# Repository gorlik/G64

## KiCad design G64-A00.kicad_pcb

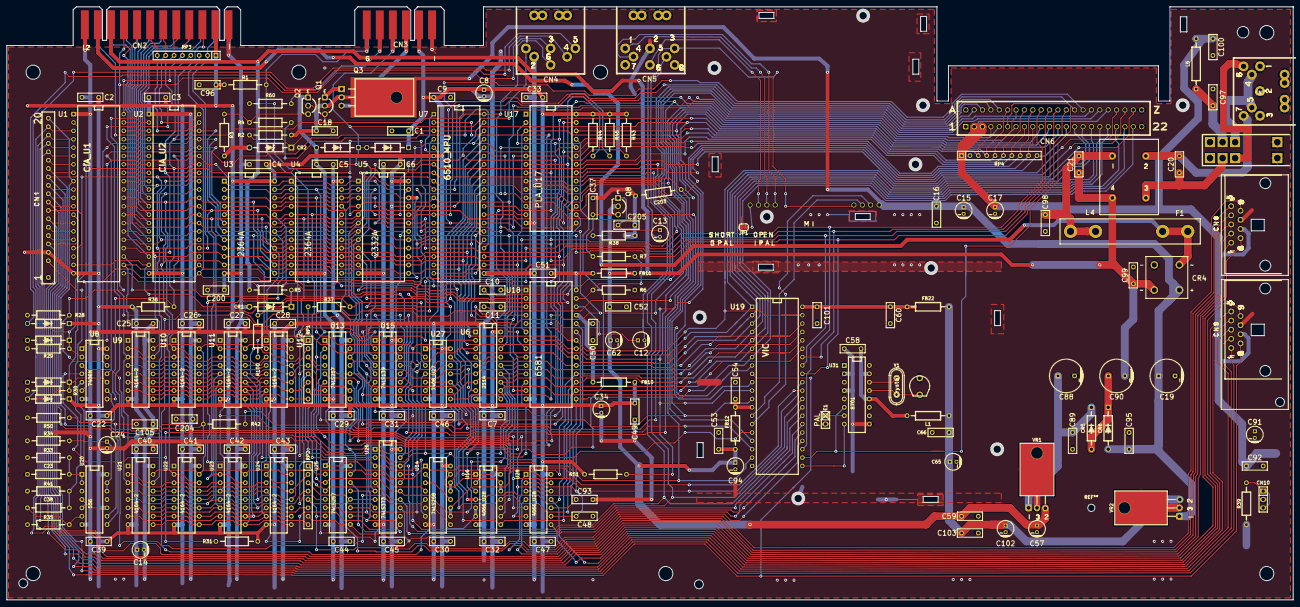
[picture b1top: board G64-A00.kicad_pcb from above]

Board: 2 copper layers, 390.0 x 179.8 mm, 181 parts (0 on the bottom side), 191 nets.

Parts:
C1, C2, C3, C4, C5, C6, C7, C9, C16, C18, C22, C25, C26, C27, C28, C29, C30, C31, C32, C33, C39, C40, C41, C42, C43, C44, C45, C46, C47, C49, C50, C51, C52, C53, C54, C59, C60, C89, C92, C95, C96, C98, C99, C101, C103, C105, C200: .1; C_film_7x2.5
C8, C12, C13, C14, C15, C17, C24, C34, C57, C62, C65, C94, C102: 10uF; CP_5p2x11
C10, C11: 470pF; C_film_7x2.5
C19: 2200uF; CP_10p5x20
C20, C21, C97, C100: .22; C_film_7x2.5
C23: 360pF; CAP_AXIAL_P12.7mm
C37: 1000pF; C_film_7x2.5
C38: 4.7nF; CAP_AXIAL_P12.7mm
C48, C93: 1800pF; C_film_7x2.5
C58: .22uF; C_film_7x2.5
C66: .1uF; C_film_7x2.5
C88: 1000uF; CP_10p5x20
C90: 470uF; CP_10p5x20
C91: 100uF; CP_5p2x11
C203: 82pF; CAPACITOR_RADIAL_P13.97_L9.9_D3.6
C204: NC; C_film_7x2.5
C205: 220pF; C_film_7x2.5
CN1: KEYBOARD_20PIN_MALE; KEYBOARD_CON
CN2: USER_PORT_CON; EDGE_CON_24P
CN3: CASSETTE_PORT_CON; EDGE_CON_12P_TAPE
CN4: SERIAL_BUS_CON; SERIAL_CON_DIN6
CN5: AV_CONN; AV_CON_DIN8
CN6: EXPANSION_PORT
CN7: POWER_CON; POWER_CON_D7_250407
CN8, CN9: CONTROL_PORT; JOYPORT_DB9
CN10: LED_CONNECTOR; pin_strip_3
CR1: IN4371; ZENER_12.7mm
CR2: IN755; ZENER_12.7mm
CR4: BRIDGE_RECTIFIER
CR5, CR6: 1N4001; RECTIFIER_TH_P12.7mm
CR9, CR12, CR13, CR14, CR15, CR16: D_Small_ALT; RECTIFIER_TH_P12.7mm
CT1: 22pF; CAP_trim_5.08mm
E1: JUMPER_WIRE; pin_strip_2
F1: 1A; FUSE
FB10, FB11, FB12, FB22: FERRITE_BEAD; FERRITE_BEAD_TH_P12.7mm
JP1: Jumper_NC_Small; SolderJumper-2_P1.3mm_Bridged_RoundedPad1.0x1.5mm
L1: L; RESISTOR
L4: CHOKE
L5: 1.2uH; INDUCTOR_P15.24mm
M1: MODULATOR_LONGBOARD; MODULATOR_PORT_LONGBOARD
Q1, Q2, Q8: 2SC1815; Q_NPN_ECB
Q3: TP29B/2SD880; TO-220-3_Horizontal_TabDown_250407
R1, R43, R44, R45: 3K3; r_0250p12_7
R2, R51: 1.5K; r_0250p12_7
R3, R7: 10K; r_0250p12_7
R4, R6, R28, R29, R30, R31, R36, R38, R100: 1K; r_0250p12_7
R5: 560; r_0250p12_7
R33, R34: 47K; r_0250p12_7
R35: 470K; r_0250p12_7
R37: 2K7; r_0250p12_7
R39: 390; r_0250p12_7
R41, R50: 1M; r_0250p12_7
R42: 82; r_0250p12_7
R60: 100; r_0250p12_7
RP1, RP2: 33R isolated; rpak_sil_8
RP3: 3K3 Bussed; rpak_sil_8
RP4: 3K3 Bussed; rpak_sil_10
SW1: POWER_SWITCH
U1: CIA_U1; DIP-40_600
U2: CIA_U2; DIP-40_600
U3, U4: 2364A; DIP-24_600
U5: 2332A; DIP-24_600
U6: 2114; DIP-18_300
U7: 6510_MPU; DIP-40_600
U8: 7406N; DIP-14_300
U9, U10, U11, U12, U21, U22, U23, U24: 4164-2; DIP-16_300
U13, U25: 74LS257; DIP-16_300
U14: 74LS258; DIP-16_300
U15: 74LS139; DIP-16_300
U16, U28: 4066_U28; DIP-14_300
U17: PLA_U17; DIP-28_600
U18: 6581; DIP-28_600
U19: VIC; DIP-40_600
U20: 556; DIP-14_300
U26: 74LS373; DIP-20_300
U27: 7408_U27; DIP-14_300
U31: 8701; DIP-16_300
VR1: 7812; VREG_TO-220-3_Horizontal_TabDown
VR2: 7805; VREG_TO-220-3_Horizontal_TabDown
Y1: Crystal; XTAL_PTH_HC-49US

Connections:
+5V: C1.1, C2.1, C3.2, C4.2, C5.2, C6.2, C7.1, C8.1, C9.1, C14.1, C17.1, C22.1, C25.1, C26.1, C27.1, C28.1, C29.2, C30.1, C31.2, C32.2, C33.1, C34.1, C39.2, C40.1, C41.1, C42.1, C43.1, C44.2, C45.1, C46.1, C47.1, C49.1, C91.1, C92.1, C96.2, C100.2, CN1.4, CN2.2, CN3.B,2, CN6.2, CN6.3, CN8.7, CN9.7, CR9.1, CR13.1, CR14.1, FB10.2, L5.1, R1.1, R28.2, R29.2, R30.2, R31.2, R33.1, R34.1, R35.1, R36.1, R39.1, R41.1, R43.1, R44.1, R45.1, R50.1, R51.2, RP3.1, RP4.1, U1.20, U2.20, U3.24, U4.24, U5.21, U5.24, U6.18, U7.6, U8.14, U9.8, U10.8, U11.8, U12.8, U13.16, U14.16, U15.16, U16.14, U17.28, U20.4, U20.10, U20.14, U21.8, U22.8, U23.8, U24.8, U25.16, U26.20, U27.1, U27.14, U28.14
+9V_UNREG: C15.1, C16.1, C18.1, C19.1, C95.1, CR4.1, CR6.2, M1.1, Q1.2, Q3.2, R2.1, VR2.1
+12V: C52.1, C53.1, C57.1, C59.1, C62.1, C94.1, FB11.2, FB12.2, Q8.2, VR1.2
/5V_IN: C97.2, L5.2, SW1.4
/9VAC: C21.2, C90.2, C99.2, CN2.10, CR4.4, L4.4, R5.1
/9VAC': CN2.11, CR4.2, F1.1
/9V_F: C21.1, C98.1, F1.2, L4.1
/9V_IN: C20.2, L4.3, SW1.1
/9V_IN': C20.1, CN7.7, L4.2
/60Hz: R37.2, U1.19, U2.19, U27.3
/ATN: CN2.9, CN4.3, R28.1, U8.12
/ATN_OUT: U2.5, U8.13
/BTNB: CN1.16, CN8.6, U1.6
/CASS_MOTOR: R4.2, U7.24
/CASS_PWR: CN3.C,3, Q3.3
/CASS_RD: CN3.D,4, CN4.1, CR9.2, CR12.1, RP3.4, U1.24
/CASS_SENSE: CN3.F,6, R1.2, U7.25
/CASS_WRT: R60.2, U7.26
/CASS_WRT': CN3.E,5, R60.1
/CLK: CN4.4, CR14.2, CR16.1, R30.1, U2.8, U8.10
/CLK_OUT: U2.6, U8.11
/CNT1: CN2.4, RP3.5, U1.40
/CNT2: CN2.6, RP3.7, U2.40
/COL0: CN1.13, CN8.1, U1.2
/COL1: CN1.19, CN8.2, U1.3
/COL2: CN1.18, CN8.3, U1.4
/COL3: CN1.17, CN8.4, U1.5
/COL5: CN1.15, U1.7
/COL6: CN1.14, U1.8, U28.6, U28.12
/COL7: CN1.20, U1.9, U28.5, U28.13
/DATA: CN4.5, CR13.2, CR15.1, R29.1, U2.9, U8.2
/DATA_OUT: U2.7, U8.1
/G64-A00_sheet2/AEC: U8.3, U14.15, U16.5, U16.6, U16.12, U16.13, U19.16, U26.1, U27.4, U27.12
/G64-A00_sheet2/AUDIO_IN: C12.2, CN5.5
/G64-A00_sheet2/AUDIO_OUT: C13.2, CN5.3, M1.4
/G64-A00_sheet2/BA: CN6.12, U17.26, U19.12, U27.9
/G64-A00_sheet2/CHROMA: M1.3, U19.14
/G64-A00_sheet2/CHROMA_O: CN5.6, M1.7
/G64-A00_sheet2/COMP_O: CN5.4, M1.5
/G64-A00_sheet2/GR\~W~: U6.10, U17.13
/G64-A00_sheet2/LUMA: M1.2, U19.15
/G64-A00_sheet2/LUMA_O: CN5.1, M1.6
/G64-A00_sheet2/MA0: RP2.4, U9.5, U10.5, U11.5, U12.5, U21.5, U22.5, U23.5, U24.5
/G64-A00_sheet2/MA1: RP2.8, U9.7, U10.7, U11.7, U12.7, U21.7, U22.7, U23.7, U24.7
/G64-A00_sheet2/MA2: RP2.6, U9.6, U10.6, U11.6, U12.6, U21.6, U22.6, U23.6, U24.6
/G64-A00_sheet2/MA3: RP2.2, U9.12, U10.12, U11.12, U12.12, U21.12, U22.12, U23.12, U24.12
/G64-A00_sheet2/MA4: RP1.4, U9.11, U10.11, U11.11, U12.11, U21.11, U22.11, U23.11, U24.11
/G64-A00_sheet2/MA5: RP1.6, U9.10, U10.10, U11.10, U12.10, U21.10, U22.10, U23.10, U24.10
/G64-A00_sheet2/MA6: RP1.2, U9.13, U10.13, U11.13, U12.13, U21.13, U22.13, U23.13, U24.13
/G64-A00_sheet2/MA7: RP1.8, U9.9, U10.9, U11.9, U12.9, U21.9, U22.9, U23.9, U24.9
/G64-A00_sheet2/SID_VCC: C50.1, FB10.1, U18.25
/G64-A00_sheet2/SID_VDD: C51.1, FB11.1, U18.28
/G64-A00_sheet2/VA0: RP2.3, U19.24, U25.12, U26.7
/G64-A00_sheet2/VA1: RP2.7, U19.25, U25.9, U26.13
/G64-A00_sheet2/VA2: RP2.5, U19.26, U25.7, U26.8
/G64-A00_sheet2/VA3: RP2.1, U19.27, U25.4, U26.14
/G64-A00_sheet2/VA4: RP1.3, U13.12, U17.20, U19.28, U26.17
/G64-A00_sheet2/VA5: RP1.5, U13.7, U17.21, U19.29, U26.18
/G64-A00_sheet2/VA6: RP1.1, U13.4, U14.4, U26.4
/G64-A00_sheet2/VA6': U14.13, U14.14, U19.30
/G64-A00_sheet2/VA7: RP1.7, U13.9, U14.7, U26.3
/G64-A00_sheet2/VA7': U14.10, U14.11, U19.31
/G64-A00_sheet2/VIC_VCC: C60.1, C101.1, FB22.1, U19.40
/G64-A00_sheet2/VIC_VDD: C54.1, FB12.1, U19.13
/G64-A00_sheet2/~AEC~: R31.1, U8.4, U13.15, U17.25, U25.15
/G64-A00_sheet2/~BASIC~: U3.20, U17.17
/G64-A00_sheet2/~CASRAM~: R42.2, U17.18
/G64-A00_sheet2/~CASRAM~': C204.2, R42.1, U9.15, U10.15, U11.15, U12.15, U21.15, U22.15, U23.15, U24.15
/G64-A00_sheet2/~CAS~: C203.2, U13.1, U14.1, U17.9, U19.19, U25.1
/G64-A00_sheet2/~CHAROM~: U5.20, U17.15
/G64-A00_sheet2/~CIAS~: U15.7, U15.15
/G64-A00_sheet2/~COLOR~: U15.6, U27.13
/G64-A00_sheet2/~DMA~: CN6.13, RP4.10, U27.5, U27.10
/G64-A00_sheet2/~EXROM~: CN6.9, RP4.9, U17.23
/G64-A00_sheet2/~GAME~: CN6.8, RP4.7, U17.22
/G64-A00_sheet2/~I\O~: U15.1, U17.12
/G64-A00_sheet2/~KERNAL: U4.20, U17.16
/G64-A00_sheet2/~RAS~: U9.4, U10.4, U11.4, U12.4, U19.18, U21.4, U22.4, U23.4, U24.4, U26.11
/G64-A00_sheet2/~ROMH~: CN6.B, U17.10
/G64-A00_sheet2/~ROML~: CN6.11, U17.11
/G64-A00_sheet2/~SID~: U15.5, U18.8
/G64-A00_sheet2/~VIC~: U15.4, U19.10
/JOYA0: CN1.12, CN9.1, U1.10
/JOYA1: CN1.11, CN9.2, U1.11
/JOYA2: CN1.10, CN9.3, U1.12
/JOYA3: CN1.5, CN9.4, U1.13
/LED+: CN10.1, CN10.3, R39.2
/PA2: CN2.M, U2.4
/PB0: CN2.C, U2.10
/PB1: CN2.D, U2.11
/PB2: CN2.E, U2.12
/PB3: CN2.F, U2.13
/PB4: CN2.H, U2.14
/PB5: CN2.J, U2.15
/PB6: CN2.K, U2.16
/PB7: CN2.L, U2.17
/POTAX: CN9.9, U28.8
/POTAY: CN9.5, U28.11
/POTBX: CN8.9, U28.1
/POTBY: CN8.5, U28.4
/ROW5: CN1.7, U1.15
/ROW6: CN1.6, U1.16
/ROW7: CN1.9, U1.17
/SP1: CN2.5, RP3.6, U1.39
/SP2: CN2.7, RP3.8, U2.39
/TRIGA: C38.1, R35.2, U20.6
/~FLAG2~: CN2.B, RP3.2, U2.24
/~PC2~: CN2.8, U2.18
/~RESTORE~: C38.2, CN1.3, R41.2
A0: CN6.Y, U1.38, U2.38, U3.8, U4.8, U5.8, U6.5, U7.7, U18.9, U25.13, U26.6
A1: CN6.X, U1.37, U2.37, U3.7, U4.7, U5.7, U6.6, U7.8, U18.10, U25.10, U26.12
A2: CN6.W, U1.36, U2.36, U3.6, U4.6, U5.6, U6.7, U7.9, U18.11, U25.6, U26.9
A3: CN6.V, U1.35, U2.35, U3.5, U4.5, U5.5, U6.4, U7.10, U18.12, U25.3, U26.15
A4: CN6.U, U3.4, U4.4, U5.4, U6.3, U7.11, U13.13, U18.13, U26.16
A5: CN6.T, U3.3, U4.3, U5.3, U6.2, U7.12, U13.6, U26.19
A6: CN6.S, U3.2, U4.2, U5.2, U6.1, U7.13, U13.3, U26.5
A7: CN6.R, U3.1, U4.1, U5.1, U6.17, U7.14, U13.10, U26.2
A8: CN6.P, U3.23, U4.23, U5.23, U6.16, U7.15, U15.14, U19.32, U25.14
A9: CN6.N, U3.22, U4.22, U5.22, U6.15, U7.16, U15.13, U19.33, U25.11
A10: CN6.M, U3.19, U4.19, U5.19, U7.17, U15.2, U19.34, U25.5
A11: CN6.L, U3.18, U4.18, U5.18, U7.18, U15.3, U19.23, U25.2
A12: CN6.K, RP4.8, U3.21, U4.21, U7.19, U13.14, U17.27
A13: CN6.J, RP4.6, U7.20, U13.5, U17.2
A14: CN6.H, RP4.5, U7.22, U13.2, U17.3
A15: CN6.F, RP4.4, U7.23, U13.11, U17.4
BTNA\~LP~: CN1.8, CN9.6, U1.14, U19.9
CAEC: U7.5, U27.6
CAN+5V: C65.1, C66.1, C102.1, C103.1, FB22.2, L1.2, VR2.2
D0: CN6.21, U1.33, U2.33, U3.9, U4.9, U5.9, U7.37, U16.11, U18.15, U19.7, U21.2, U21.14
D1: CN6.20, U1.32, U2.32, U3.10, U4.10, U5.10, U7.36, U9.2, U9.14, U16.8, U18.16, U19.6
D2: CN6.19, U1.31, U2.31, U3.11, U4.11, U5.11, U7.35, U16.4, U18.17, U19.5, U22.2, U22.14
D3: CN6.18, U1.30, U2.30, U3.13, U4.13, U5.13, U7.34, U10.2, U10.14, U16.1, U18.18, U19.4
D4: CN6.17, U1.29, U2.29, U3.14, U4.14, U5.14, U7.33, U18.19, U19.3, U23.2, U23.14
D5: CN6.16, U1.28, U2.28, U3.15, U4.15, U5.15, U7.32, U11.2, U11.14, U18.20, U19.2
D6: CN6.15, U1.27, U2.27, U3.16, U4.16, U5.16, U7.31, U18.21, U19.1, U24.2, U24.14
D7: CN6.14, U1.26, U2.26, U3.17, U4.17, U5.17, U7.30, U12.2, U12.14, U18.22, U19.39
DOT_CLOCK: CN6.6, U19.22, U31.6
GND: C1.2, C2.2, C3.1, C4.1, C5.1, C6.1, C7.2, C8.2, C9.2, C14.2, C15.2, C16.2, C17.2, C19.2, C22.2, C23.2, C24.2, C25.2, C26.2, C27.2, C28.2, C29.1, C30.2, C31.1, C32.1, C33.2, C34.2, C37.2, C39.1, C40.2, C41.2, C42.2, C43.2, C44.1, C45.2, C46.2, C47.2, C48.2, C49.2, C50.2, C51.2, C52.2, C53.2, C54.2, C57.2, C58.2, C59.2, C60.2, C62.2, C65.2, C66.2, C88.2, C89.2, C91.2, C92.2, C93.2, C94.2, C95.2, C96.1, C97.1, C98.2, C99.1, C100.1, C101.2, C102.2, C103.2, C105.1, C200.2, C203.1, C204.1, C205.2, CN1.1, CN2.1, CN2.12, CN2.A, CN2.N, CN3.A,1, CN4.2, CN5.2, CN6.1, CN6.22, CN6.A, CN6.Z, CN7.1, CN7.2, CN7.3, CN8.8, CN9.8, CN10.2, CR1.2, CR2.2, CR4.3, CR12.2, CR15.2, CR16.2, CT1.2, E1.2, JP1.2, Q2.1, R3.2, R6.1, R38.1, SW1.pe, U1.1, U2.1, U3.12, U4.12, U5.12, U6.9, U7.21, U8.7, U9.16, U10.16, U11.16, U12.16, U13.8, U14.8, U15.8, U16.7, U17.14, U17.19, U18.14, U19.20, U20.7, U21.16, U22.16, U23.16, U24.16, U25.8, U26.10, U27.7, U28.7, U31.2, U31.4, U31.9, VR1.3, VR2.3
unnamed: C10.1, U18.1
unnamed: C10.2, U18.2
unnamed: C11.1, U18.3
unnamed: C11.2, U18.4
unnamed: C12.1, U18.26
unnamed: C13.1, C205.1, Q8.1, R38.2
unnamed: C18.2, CR2.1, Q1.3, Q2.2, R2.2
unnamed: C23.1, R33.2, U20.1, U20.2
unnamed: C24.1, R34.2, U20.12, U20.13
unnamed: C37.1, Q8.3, R7.1
unnamed: C58.1, L1.1, U31.12, U31.15
unnamed: C88.1, C89.1, CR5.1, VR1.1
unnamed: C90.1, CR5.2, CR6.1
unnamed: C105.2, R50.2, U20.8
unnamed: C200.1, CR1.1, R5.2, R100.1
unnamed: CN6.7, U15.10
unnamed: CN6.10, U15.9
unnamed: CN7.4, CN7.5, SW1.5
unnamed: CN7.6, SW1.2
unnamed: CT1.1, U31.13, Y1.2
unnamed: E1.1, U31.7
unnamed: JP1.1, M1.8
unnamed: Q1.1, Q3.1
unnamed: Q2.3, R3.1, R4.1
unnamed: R6.2, R7.2, U18.27
unnamed: R37.1, R100.2, U27.2
unnamed: U14.6, U14.9
unnamed: U14.3, U14.12
unnamed: U6.11, U16.2, U19.35
unnamed: U6.12, U16.3, U19.36
unnamed: U6.13, U16.9, U19.37
unnamed: U6.14, U16.10, U19.38
unnamed: U8.5, U20.5
unnamed: U8.9, U20.9
unnamed: U6.8, U27.11
unnamed: U31.14, Y1.1
PHI0: U7.1, U19.17
PHI2: CN6.E, U1.25, U2.25, U7.39, U18.6
PHI_COLOR: U19.21, U31.8
POTX: C48.1, U18.24, U28.2, U28.9
POTY: C93.1, U18.23, U28.3, U28.10
RDY: U7.2, U27.8
R\~W~: CN6.5, R51.1, U1.22, U2.22, U7.38, U9.3, U10.3, U11.3, U12.3, U17.24, U18.7, U19.11, U21.3, U22.3, U23.3, U24.3
~CHAREN~: R43.2, U7.27, U17.6
~CIA1~: U1.23, U15.12
~CIA2~: U2.23, U15.11
~HIRAM~: R44.2, U7.28, U17.7
~IRQ~: CN6.4, RP4.3, U1.21, U7.3, U19.8
~LORAM~: R45.2, U7.29, U17.8
~NMI~: CN6.D, RP3.3, U2.21, U7.4, U8.6
~RESET~: CN2.3, CN4.6, CN6.C, R36.2, U1.34, U2.34, U7.40, U8.8, U18.5
~VA14~: U2.2, U14.2, U17.5
~VA15~: U2.3, U14.5

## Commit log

2022-08-09 initial commit. selected files from https://github.com/bwack/C64-250407-Replica-KiCad
2022-08-09 remove execute permission
2022-08-09 rename schematics and pcb libraries add C64-discrete-library for the missing symbols fix symbol references in sch and pcb
2022-08-09 fix pin properties reduce number of ERC errors/warnings
2022-08-09 change Earth net to GND fix PCB DRC fix slanted PCB edge
2022-08-09 use C64 specific power symbol
2022-08-10 add assy 250425 schematics add 8701 to schematics library
2022-08-10 add assy 250466 schematics add 4464 and 5way RPAK schematics symbols
2022-08-10 replace FUSE and LED connector symbols with new ones closer to original schematics replace 1N4001 with generic Diode_small
2022-08-11 repalce fuse symbol on 250407
2022-08-11 add variable capacitor symbol to libnrary
2022-08-26 update RPACK symbols. add NO CONNECT to switch pins
2022-08-26 update BRIDGE RECTIFIER symbol remove redundant tracks
2022-08-26 add several 3D models update footprints and PCB
2022-08-26 rename RPACKS add 78xx and 78xx-alt
2022-08-26 initial checkin from 250407
2022-08-26 remove via mask opening
2022-08-26 change vias to 0.4/0.9 add netclass for power and clocks
2022-08-28 update many components on the PCB
2022-08-28 add protection diodes to PCB
2022-08-28 change DIN footprints to accept both 5mm and 10mm retention add link to 3D models for a few footprints
2022-08-29 update edge connectors
2022-08-29 remove EMI ferrite beads
2022-08-29 replace discrete clock generation with MOS8701
2022-08-29 add extra protection diodes on IEC port

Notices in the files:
G64-A00.kicad_pcb:
Licensed under CERN OHL v.1.2
